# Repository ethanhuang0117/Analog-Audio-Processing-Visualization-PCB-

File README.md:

# Analog Audio Processing & Visualization PCB

A custom analog audio spectrum analyzer PCB that processes microphone audio across 8 frequency bands and displays signal intensity using 4-level LED indicators.

### Demo

[Download and Watch the PCB Demo](images/demo.mp4)

## Overview

The system captures audio through an electret microphone, amplifies the signal, separates it into 8 frequency bands using active filters, and displays the signal intensity through LED indicators.

**System Chain:**

Microphone → Preamp → 8-Band Filters → Envelope Detection → Comparators → LED Visualization

## Features

- 8 frequency bands spanning approximately 80 Hz – 10 kHz
- Cascaded Sallen-Key active filters for improved frequency separation
- Microphone preamplification for low-level audio signals
- Envelope detection to convert AC audio signals into DC levels
- 4-level LED intensity indication for each frequency band using comparators
- USB 5 V single-supply
- Custom PCB designed and assembled in KiCad

## Frequency Bands

| Band | Centre Frequency |
|---|---:|
| 1 | 80 Hz |
| 2 | 160 Hz |
| 3 | 320 Hz |
| 4 | 640 Hz |
| 5 | 1.25 kHz |
| 6 | 2.5 kHz |
| 7 | 5 kHz |
| 8 | 10 kHz |

## Filter Design

The initial design used passive filters, but were redesigned using cascaded Sallen-Key active filters to achieve greater roll-off and band separation.

### Sallen-Key Bandpass Filter Calculations

Each frequency band consists of a cascaded 2nd order Sallen-Key High Pass Filter (HPF) and Low Pass Filter (LPF).

**Assumptions:**
- $R_1 = R_2 = R$
- $C_1 = C_2 = C$
- $C = 100\text{nF}$ (Bands 1-4), $C = 10\text{nF}$ (Bands 5-8)

The cutoff frequencies are spaced by $\sqrt{2}$ from the centre frequency.

$$f_H = f_0 \times \sqrt{2}$$

$$f_L = \frac{f_0}{\sqrt{2}}$$

The general Sallen-Key cutoff frequency formula before simplification is:

$$f = \frac{1}{2\pi\sqrt{R_1 R_2 C_1 C_2}}$$

Applying the assumptions $R_1 = R_2 = R$ and $C_1 = C_2 = C$, this simplifies to:

$$f = \frac{1}{2\pi RC}$$

Rearranging for $R$:

$$R = \frac{1}{2\pi f C}$$

---

### Band 4 Example (Centre frequency: 640Hz)

**Step 1: Calculate HPF cutoff frequency**

$$f_L = \frac{f_0}{\sqrt{2}} = \frac{640}{\sqrt{2}} = 453\text{Hz}$$

**Step 2: Calculate LPF cutoff frequency**

$$f_H = f_0 \times \sqrt{2} = 640 \times \sqrt{2} = 905\text{Hz}$$

**Step 3: Calculate HPF resistor value ($C = 100\text{nF}$)**

$$R_{HPF} = \frac{1}{2\pi \times 453 \times 100 \times 10^{-9}} = 3513\Omega \approx 3.6\text{k}\Omega$$

**Step 4: Calculate LPF resistor value ($C = 100\text{nF}$)**

$$R_{LPF} = \frac{1}{2\pi \times 905 \times 100 \times 10^{-9}} = 1759\Omega \approx 1.8\text{k}\Omega$$

---

### Filter Band Summary

| Band | Centre Frequency | C | HPF Cutoff | HPF R | LPF Cutoff | LPF R |
|------|-----------------|---|------------|-------|------------|-------|
| 1 | 80Hz | 100nF | 56.6Hz | 27kΩ | 113Hz | 15kΩ |
| 2 | 160Hz | 100nF | 113Hz | 15kΩ | 226Hz | 6.8kΩ |
| 3 | 320Hz | 100nF | 226Hz | 6.8kΩ | 453Hz | 3.6kΩ |
| 4 | 640Hz | 100nF | 453Hz | 3.6kΩ | 905Hz | 1.8kΩ |
| 5 | 1.25kHz | 10nF | 884Hz | 18kΩ | 1.77kHz | 9.1kΩ |
| 6 | 2.5kHz | 10nF | 1.77kHz | 9.1kΩ | 3.54kHz | 4.7kΩ |
| 7 | 5kHz | 10nF | 3.54kHz | 4.7kΩ | 7.07kHz | 2.2kΩ |
| 8 | 10kHz | 10nF | 7.07kHz | 2.2kΩ | 14.1kHz | 1.1kΩ |

## Circuit Design

### Power

The circuit operates from a 5 V USB supply. Since audio signals oscillate about a center point, a virtual ground of 2.5V is used to allow the analog signal stages to operate from a single supply.

### Microphone & Preamplifier

A CMA-4544PF-W electret microphone captures the incoming audio signal, which is amplified using an MCP6004 op-amp to provide a suitable signal level for the filter stages.

The CMA-4544PF-W was chosen because its frequency response of 20Hz-20kHz covers the full audio spectrum.

### Envelope Detection

Each filtered signal passes through an envelope detector to convert the AC waveform into a varying DC voltage proportional to its amplitude.

The RC time constant determines the decay time of the envelope:

$$\tau = R \times C = 47\text{k}\Omega \times 4.7\mu\text{F} = 221\text{ms}$$

This gives a smooth, natural decay that visually tracks the music without flickering too fast or responding too sluggishly.

### Comparator & LED Stage

Comparator circuits divide each detected signal into four amplitude thresholds. The resulting outputs drive four LEDs per frequency band to provide a 4-level visualization of audio intensity.

## Prototyping & Testing

Individual circuit stages were first tested on breadboards and simulated in Multisim before PCB fabrication.

This iterative testing helped identify design issues before fabrication and reduced the need for PCB rework.

## PCB Design

The validated circuit was translated into a custom PCB using KiCad, with component placement, routing, and ground pours optimized for a compact and reliable layout.

### 3D PCB View

### Schematic

[View Full Schematic (PDF)](Schematic.pdf)

## Results

The completed PCB successfully processes audio through the 8 frequency bands and provides visual feedback through the LED array.

## Design Challenges & Iterations

### Passive → Active Filter Redesign

The original passive filter approach did not provide sufficient frequency separation. Sallen-Key active filters were implemented to improve roll-off and isolation between adjacent bands.

### Gain Optimization

The preamplifier gain was iteratively adjusted during breadboard testing to provide sufficient signal amplitude without excessive amplification of noise.

### Single-Supply Operation

Because the circuit operates from a 5 V USB supply, a virtual ground was implemented to allow the op-amp stages to process audio signals within the available supply range.

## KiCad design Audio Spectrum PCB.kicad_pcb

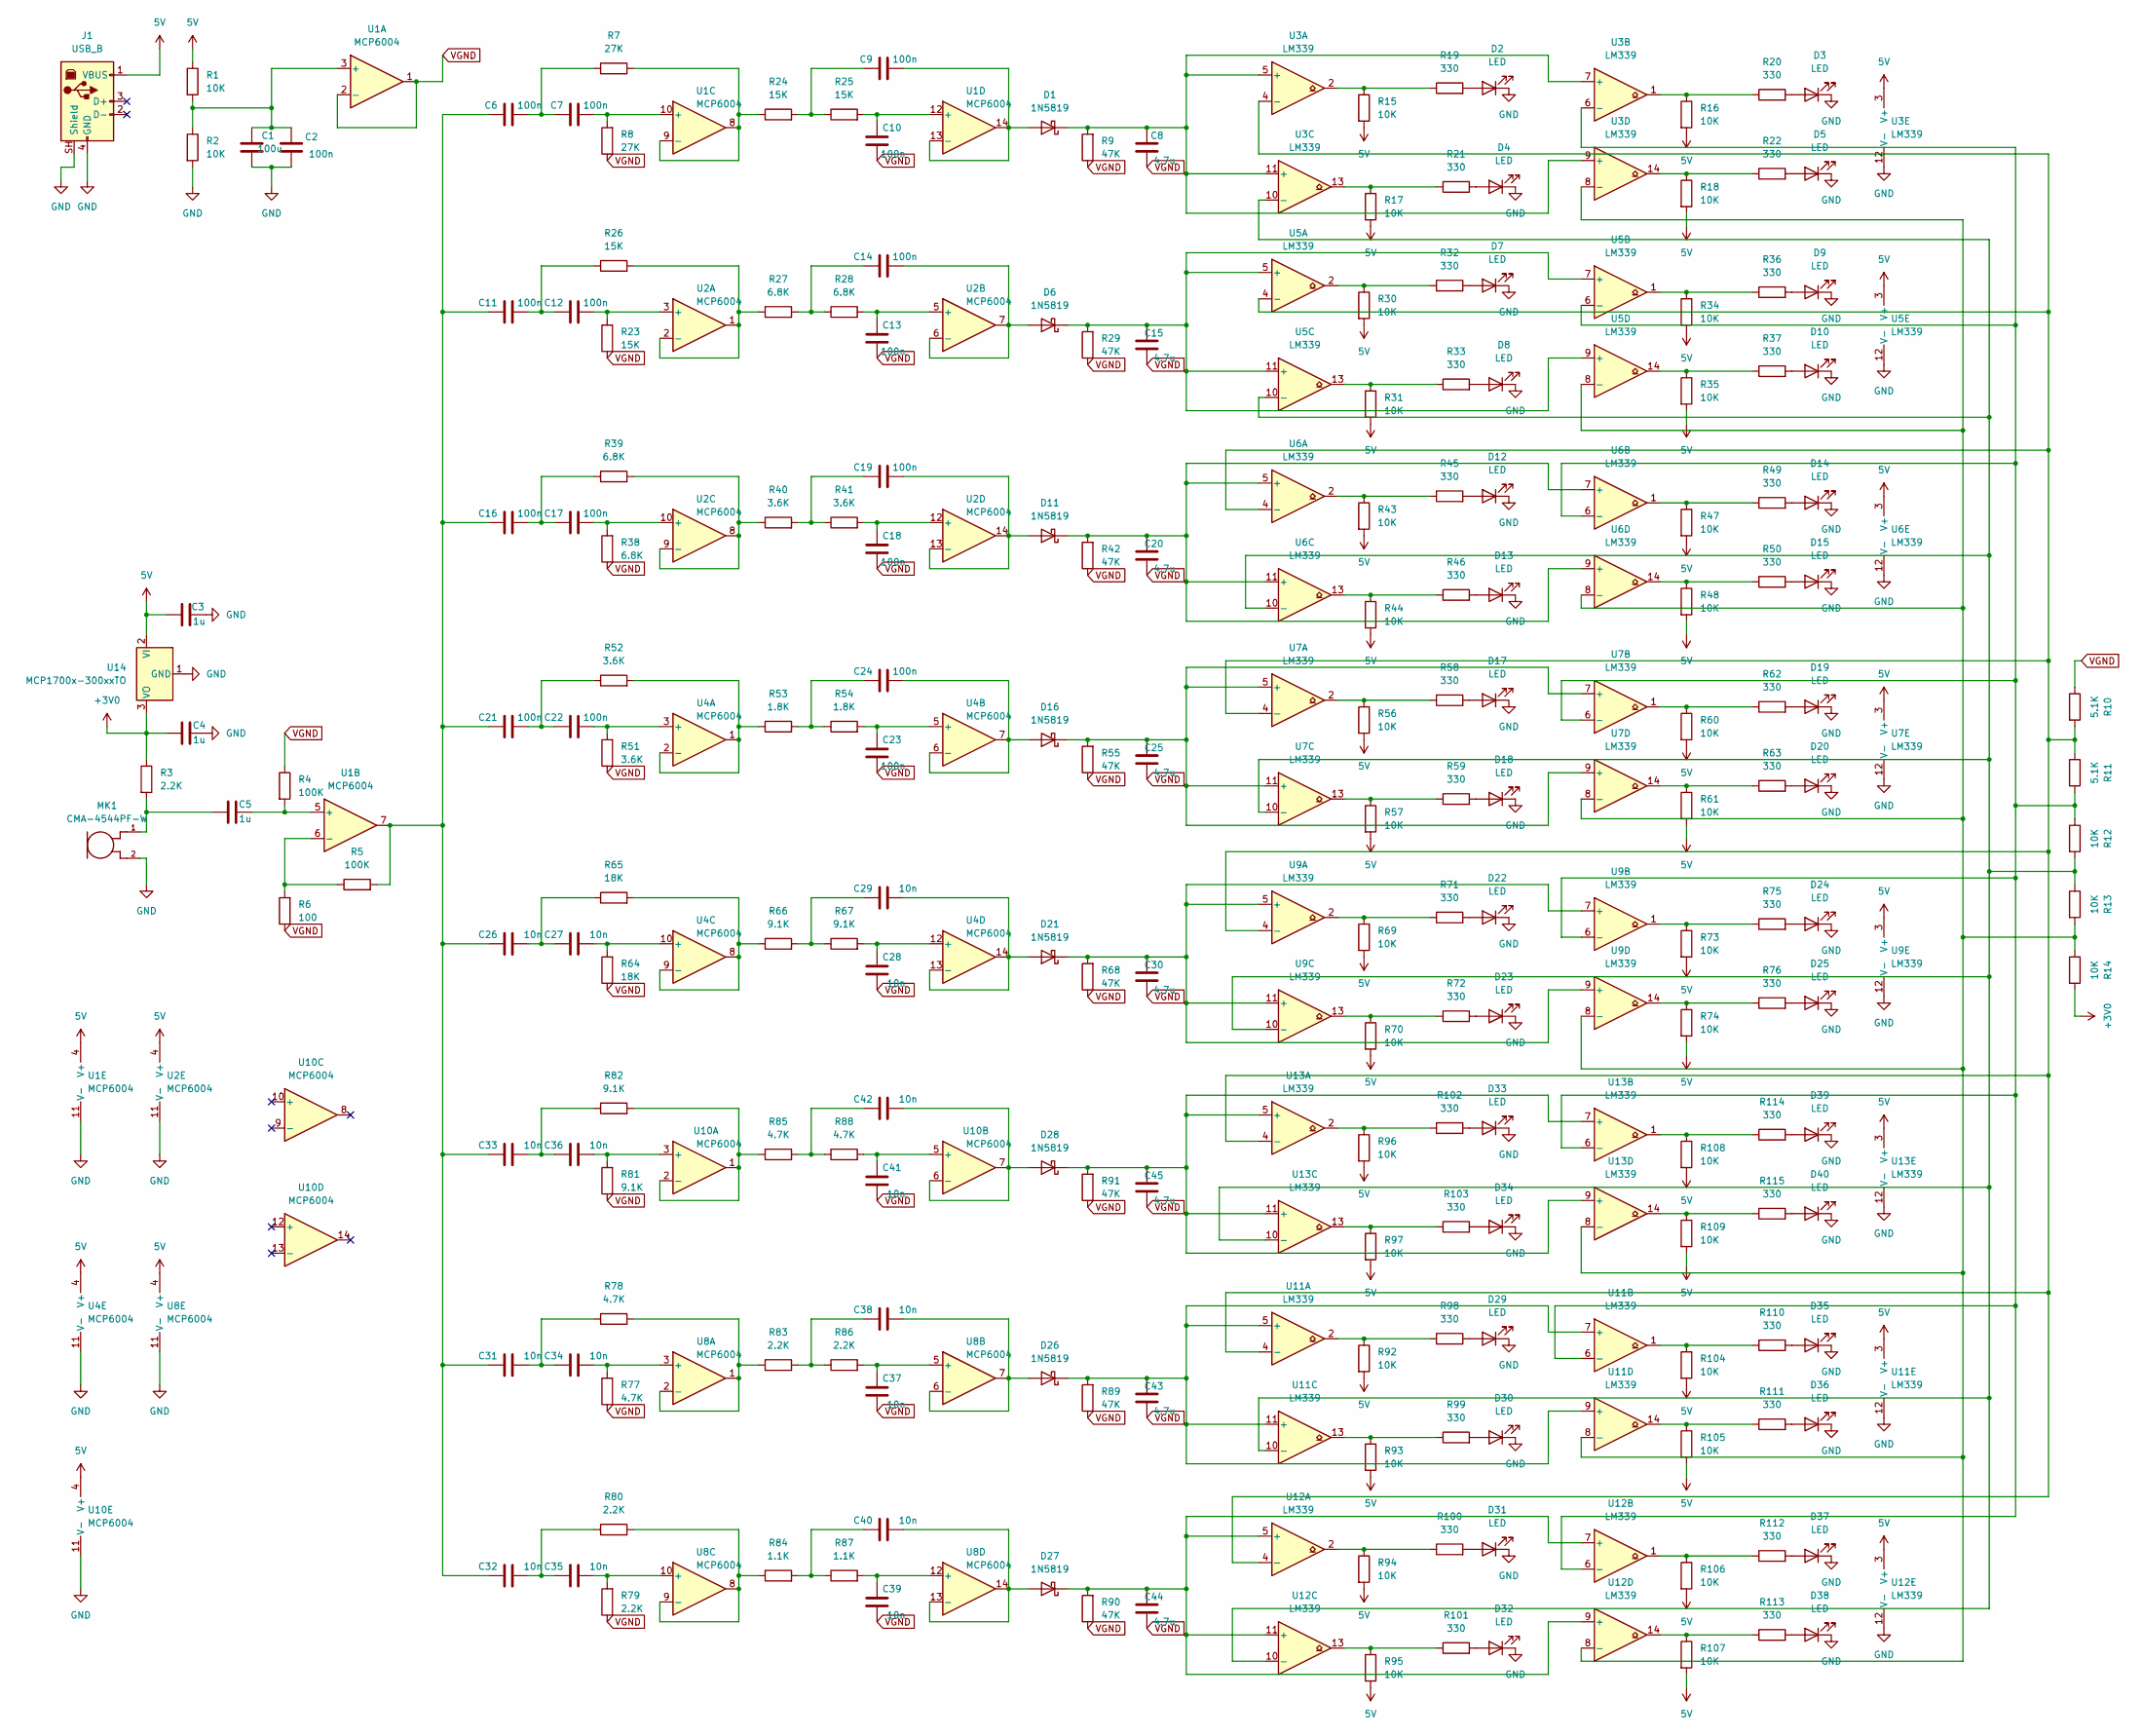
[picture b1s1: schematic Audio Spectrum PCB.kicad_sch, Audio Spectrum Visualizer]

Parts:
C1: 100u; CP_Radial_D5.0mm_P2.00mm
C2, C6, C7, C9, C10, C11, C12, C13, C14, C16, C17, C18, C19, C21, C22, C23, C24: 100n; C_Disc_D5.0mm_W2.5mm_P2.50mm
C3, C4, C5: 1u; CP_Radial_D5.0mm_P2.00mm
C8, C15, C20, C25, C30, C43, C44, C45: 4.7u; CP_Radial_D5.0mm_P2.00mm
C26, C27, C28, C29, C31, C32, C33, C34, C35, C36, C37, C38, C39, C40, C41, C42: 10n; C_Disc_D5.0mm_W2.5mm_P5.00mm
D1, D6, D11, D16, D21, D26, D27, D28: 1N5819; D_DO-41_SOD81_P10.16mm_Horizontal
D2, D3, D4, D5, D7, D8, D9, D10, D12, D13, D14, D15, D17, D18, D19, D20, D22, D23, D24, D25, D29, D30, D31, D32, D33, D34, D35, D36, D37, D38, D39, D40: LED; LED_D5.0mm
J1: USB_B; USB_B_OST_USB-B1HSxx_Horizontal
MK1: CMA-4544PF-W; MIC_CMA-4544PF-W
R1, R2, R12, R13, R14, R15, R16, R17, R18, R30, R31, R34, R35, R43, R44, R47, R48, R56, R57, R60, R61, R69, R70, R73, R74, R92, R93, R94, R95, R96, R97, R104, R105, R106, R107, R108, R109: 10K; R_Axial_DIN0207_L6.3mm_D2.5mm_P10.16mm_Horizontal
R3, R79, R80, R83, R86: 2.2K; R_Axial_DIN0207_L6.3mm_D2.5mm_P10.16mm_Horizontal
R4, R5: 100K; R_Axial_DIN0207_L6.3mm_D2.5mm_P10.16mm_Horizontal
R6: 100; R_Axial_DIN0207_L6.3mm_D2.5mm_P10.16mm_Horizontal
R7, R8: 27K; R_Axial_DIN0207_L6.3mm_D2.5mm_P10.16mm_Horizontal
R9, R29, R42, R55, R68, R89, R90, R91: 47K; R_Axial_DIN0207_L6.3mm_D2.5mm_P10.16mm_Horizontal
R10, R11: 5.1K; R_Axial_DIN0207_L6.3mm_D2.5mm_P10.16mm_Horizontal
R19, R20, R21, R22, R32, R33, R36, R37, R45, R46, R49, R50, R58, R59, R62, R63, R71, R72, R75, R76, R98, R99, R100, R101, R102, R103, R110, R111, R112, R113, R114, R115: 330; R_Axial_DIN0207_L6.3mm_D2.5mm_P10.16mm_Horizontal
R23, R24, R25, R26: 15K; R_Axial_DIN0207_L6.3mm_D2.5mm_P10.16mm_Horizontal
R27, R28, R38, R39: 6.8K; R_Axial_DIN0207_L6.3mm_D2.5mm_P10.16mm_Horizontal
R40, R41, R51, R52: 3.6K; R_Axial_DIN0207_L6.3mm_D2.5mm_P10.16mm_Horizontal
R53, R54: 1.8K; R_Axial_DIN0207_L6.3mm_D2.5mm_P10.16mm_Horizontal
R64, R65: 18K; R_Axial_DIN0207_L6.3mm_D2.5mm_P10.16mm_Horizontal
R66, R67, R81, R82: 9.1K; R_Axial_DIN0207_L6.3mm_D2.5mm_P10.16mm_Horizontal
R77, R78, R85, R88: 4.7K; R_Axial_DIN0207_L6.3mm_D2.5mm_P10.16mm_Horizontal
R84, R87: 1.1K; R_Axial_DIN0207_L6.3mm_D2.5mm_P10.16mm_Horizontal
U1, U2, U4, U8, U10: MCP6004; DIP-14_W7.62mm
U3, U5, U6, U7, U9, U11, U12, U13: LM339; DIP-14_W7.62mm
U14: MCP1700x-300xxTO; TO-92_Inline

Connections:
5V: C3.1, J1.1 (VBUS), R1.1, R15.2, R16.2, R17.2, R18.2, R30.2, R31.2, R34.2, R35.2, R43.2, R44.2, R47.2, R48.2, R56.2, R57.2, R60.2, R61.2, R69.2, R70.2, R73.2, R74.2, R92.2, R93.2, R94.2, R95.2, R96.2, R97.2, R104.2, R105.2, R106.2, R107.2, R108.2, R109.2, U1.4 (V+), U2.4 (V+), U3.3 (V+), U4.4 (V+), U5.3 (V+), U6.3 (V+), U7.3 (V+), U8.4 (V+), U9.3 (V+), U10.4 (V+), U11.3 (V+), U12.3 (V+), U13.3 (V+), U14.2 (VI)
+3V0: C4.1, R3.1, R14.2, U14.3 (VO)
GND: C1.2, C2.2, C3.2, C4.2, D2.1 (K), D3.1 (K), D4.1 (K), D5.1 (K), D7.1 (K), D8.1 (K), D9.1 (K), D10.1 (K), D12.1 (K), D13.1 (K), D14.1 (K), D15.1 (K), D17.1 (K), D18.1 (K), D19.1 (K), D20.1 (K), D22.1 (K), D23.1 (K), D24.1 (K), D25.1 (K), D29.1 (K), D30.1 (K), D31.1 (K), D32.1 (K), D33.1 (K), D34.1 (K), D35.1 (K), D36.1 (K), D37.1 (K), D38.1 (K), D39.1 (K), D40.1 (K), J1.4 (GND), J1.SH (Shield), MK1.2, R2.2, U1.11 (V-), U2.11 (V-), U3.12 (V-), U4.11 (V-), U5.12 (V-), U6.12 (V-), U7.12 (V-), U8.11 (V-), U9.12 (V-), U10.11 (V-), U11.12 (V-), U12.12 (V-), U13.12 (V-), U14.1 (GND)
unnamed: C5.1, MK1.1, R3.2
unnamed: C6.2, C7.1, R7.1
unnamed: C9.1, R24.2, R25.1
unnamed: C6.1, C11.1, C16.1, C21.1, C26.1, C31.1, C32.1, C33.1, R5.2, U1.7
unnamed: C11.2, C12.1, R26.1
unnamed: C14.1, R27.2, R28.1
unnamed: C16.2, C17.1, R39.1
unnamed: C19.1, R40.2, R41.1
unnamed: C21.2, C22.1, R52.1
unnamed: C24.1, R53.2, R54.1
unnamed: C26.2, C27.1, R65.1
unnamed: C29.1, R66.2, R67.1
unnamed: C31.2, C34.1, R78.1
unnamed: C32.2, C35.1, R80.1
unnamed: C33.2, C36.1, R82.1
unnamed: C38.1, R83.2, R86.1
unnamed: C40.1, R84.2, R87.1
unnamed: C42.1, R85.2, R88.1
unnamed: C9.2, D1.2 (A), U1.13 (-), U1.14
unnamed: C8.2, D1.1 (K), R9.2, U3.5 (+), U3.7 (+), U3.9 (+), U3.11 (+)
unnamed: D2.2 (A), R19.2
unnamed: D3.2 (A), R20.2
unnamed: D4.2 (A), R21.2
unnamed: D5.2 (A), R22.2
unnamed: C14.2, D6.2 (A), U2.6 (-), U2.7
unnamed: C15.2, D6.1 (K), R29.2, U5.5 (+), U5.7 (+), U5.9 (+), U5.11 (+)
unnamed: D7.2 (A), R32.2
unnamed: D8.2 (A), R33.2
unnamed: D9.2 (A), R36.2
unnamed: D10.2 (A), R37.2
unnamed: C19.2, D11.2 (A), U2.13 (-), U2.14
unnamed: C20.2, D11.1 (K), R42.2, U6.5 (+), U6.7 (+), U6.9 (+), U6.11 (+)
unnamed: D12.2 (A), R45.2
unnamed: D13.2 (A), R46.2
unnamed: D14.2 (A), R49.2
unnamed: D15.2 (A), R50.2
unnamed: C24.2, D16.2 (A), U4.6 (-), U4.7
unnamed: C25.2, D16.1 (K), R55.2, U7.5 (+), U7.7 (+), U7.9 (+), U7.11 (+)
unnamed: D17.2 (A), R58.2
unnamed: D18.2 (A), R59.2
unnamed: D19.2 (A), R62.2
unnamed: D20.2 (A), R63.2
unnamed: C29.2, D21.2 (A), U4.13 (-), U4.14
unnamed: C30.2, D21.1 (K), R68.2, U9.5 (+), U9.7 (+), U9.9 (+), U9.11 (+)
unnamed: D22.2 (A), R71.2
unnamed: D23.2 (A), R72.2
unnamed: D24.2 (A), R75.2
unnamed: D25.2 (A), R76.2
unnamed: C38.2, D26.2 (A), U8.6 (-), U8.7
unnamed: C43.2, D26.1 (K), R89.2, U11.5 (+), U11.7 (+), U11.9 (+), U11.11 (+)
unnamed: C40.2, D27.2 (A), U8.13 (-), U8.14
unnamed: C44.2, D27.1 (K), R90.2, U12.5 (+), U12.7 (+), U12.9 (+), U12.11 (+)
unnamed: C42.2, D28.2 (A), U10.6 (-), U10.7
unnamed: C45.2, D28.1 (K), R91.2, U13.5 (+), U13.7 (+), U13.9 (+), U13.11 (+)
unnamed: D29.2 (A), R98.2
unnamed: D30.2 (A), R99.2
unnamed: D31.2 (A), R100.2
unnamed: D32.2 (A), R101.2
unnamed: D33.2 (A), R102.2
unnamed: D34.2 (A), R103.2
unnamed: D35.2 (A), R110.2
unnamed: D36.2 (A), R111.2
unnamed: D37.2 (A), R112.2
unnamed: D38.2 (A), R113.2
unnamed: D39.2 (A), R114.2
unnamed: D40.2 (A), R115.2
unnamed: R15.1, R19.1, U3.2
unnamed: R16.1, R20.1, U3.1
unnamed: R17.1, R21.1, U3.13
unnamed: R18.1, R22.1, U3.14
unnamed: R30.1, R32.1, U5.2
unnamed: R31.1, R33.1, U5.13
unnamed: R34.1, R36.1, U5.1
unnamed: R35.1, R37.1, U5.14
unnamed: R43.1, R45.1, U6.2
unnamed: R44.1, R46.1, U6.13
unnamed: R47.1, R49.1, U6.1
unnamed: R48.1, R50.1, U6.14
unnamed: R56.1, R58.1, U7.2
unnamed: R57.1, R59.1, U7.13
unnamed: R60.1, R62.1, U7.1
unnamed: R61.1, R63.1, U7.14
unnamed: R69.1, R71.1, U9.2
unnamed: R70.1, R72.1, U9.13
unnamed: R73.1, R75.1, U9.1
unnamed: R74.1, R76.1, U9.14
unnamed: R92.1, R98.1, U11.2
unnamed: R93.1, R99.1, U11.13
unnamed: R94.1, R100.1, U12.2
unnamed: R95.1, R101.1, U12.13
unnamed: R96.1, R102.1, U13.2
unnamed: R97.1, R103.1, U13.13
unnamed: R104.1, R110.1, U11.1
unnamed: R105.1, R111.1, U11.14
unnamed: R106.1, R112.1, U12.1
unnamed: R107.1, R113.1, U12.14
unnamed: R108.1, R114.1, U13.1
unnamed: R109.1, R115.1, U13.14
unnamed: C1.1, C2.1, R1.2, R2.1, U1.3 (+)
unnamed: C5.2, R4.2, U1.5 (+)
unnamed: R5.1, R6.2, U1.6 (-)
unnamed: C7.2, R8.2, U1.10 (+)
unnamed: R7.2, R24.1, U1.8, U1.9 (-)
unnamed: C10.2, R25.2, U1.12 (+)
unnamed: C12.2, R23.2, U2.3 (+)
unnamed: R26.2, R27.1, U2.1, U2.2 (-)
unnamed: C13.2, R28.2, U2.5 (+)
unnamed: C17.2, R38.2, U2.10 (+)
unnamed: R39.2, R40.1, U2.8, U2.9 (-)
unnamed: C18.2, R41.2, U2.12 (+)
unnamed: C22.2, R51.2, U4.3 (+)
unnamed: R52.2, R53.1, U4.1, U4.2 (-)
unnamed: C23.2, R54.2, U4.5 (+)
unnamed: C27.2, R64.2, U4.10 (+)
unnamed: R65.2, R66.1, U4.8, U4.9 (-)
unnamed: C28.2, R67.2, U4.12 (+)
unnamed: C34.2, R77.2, U8.3 (+)
unnamed: R78.2, R83.1, U8.1, U8.2 (-)
unnamed: C37.2, R86.2, U8.5 (+)
unnamed: C35.2, R79.2, U8.10 (+)
unnamed: R80.2, R84.1, U8.8, U8.9 (-)
unnamed: C39.2, R87.2, U8.12 (+)
unnamed: C36.2, R81.2, U10.3 (+)
unnamed: R82.2, R85.1, U10.1, U10.2 (-)
unnamed: C41.2, R88.2, U10.5 (+)
unnamed: R10.2, R11.1, U3.4 (-), U5.4 (-), U6.4 (-), U7.4 (-), U9.4 (-), U11.4 (-), U12.4 (-), U13.4 (-)
unnamed: R11.2, R12.1, U3.6 (-), U5.6 (-), U6.6 (-), U7.6 (-), U9.6 (-), U11.6 (-), U12.6 (-), U13.6 (-)
unnamed: R12.2, R13.1, U3.10 (-), U5.10 (-), U6.10 (-), U7.10 (-), U9.10 (-), U11.10 (-), U12.10 (-), U13.10 (-)
unnamed: R13.2, R14.1, U3.8 (-), U5.8 (-), U6.8 (-), U7.8 (-), U9.8 (-), U11.8 (-), U12.8 (-), U13.8 (-)
VGND: C8.1, C10.1, C13.1, C15.1, C18.1, C20.1, C23.1, C25.1, C28.1, C30.1, C37.1, C39.1, C41.1, C43.1, C44.1, C45.1, R4.1, R6.1, R8.1, R9.1, R10.1, R23.1, R29.1, R38.1, R42.1, R51.1, R55.1, R64.1, R68.1, R77.1, R79.1, R81.1, R89.1, R90.1, R91.1, U1.1, U1.2 (-)

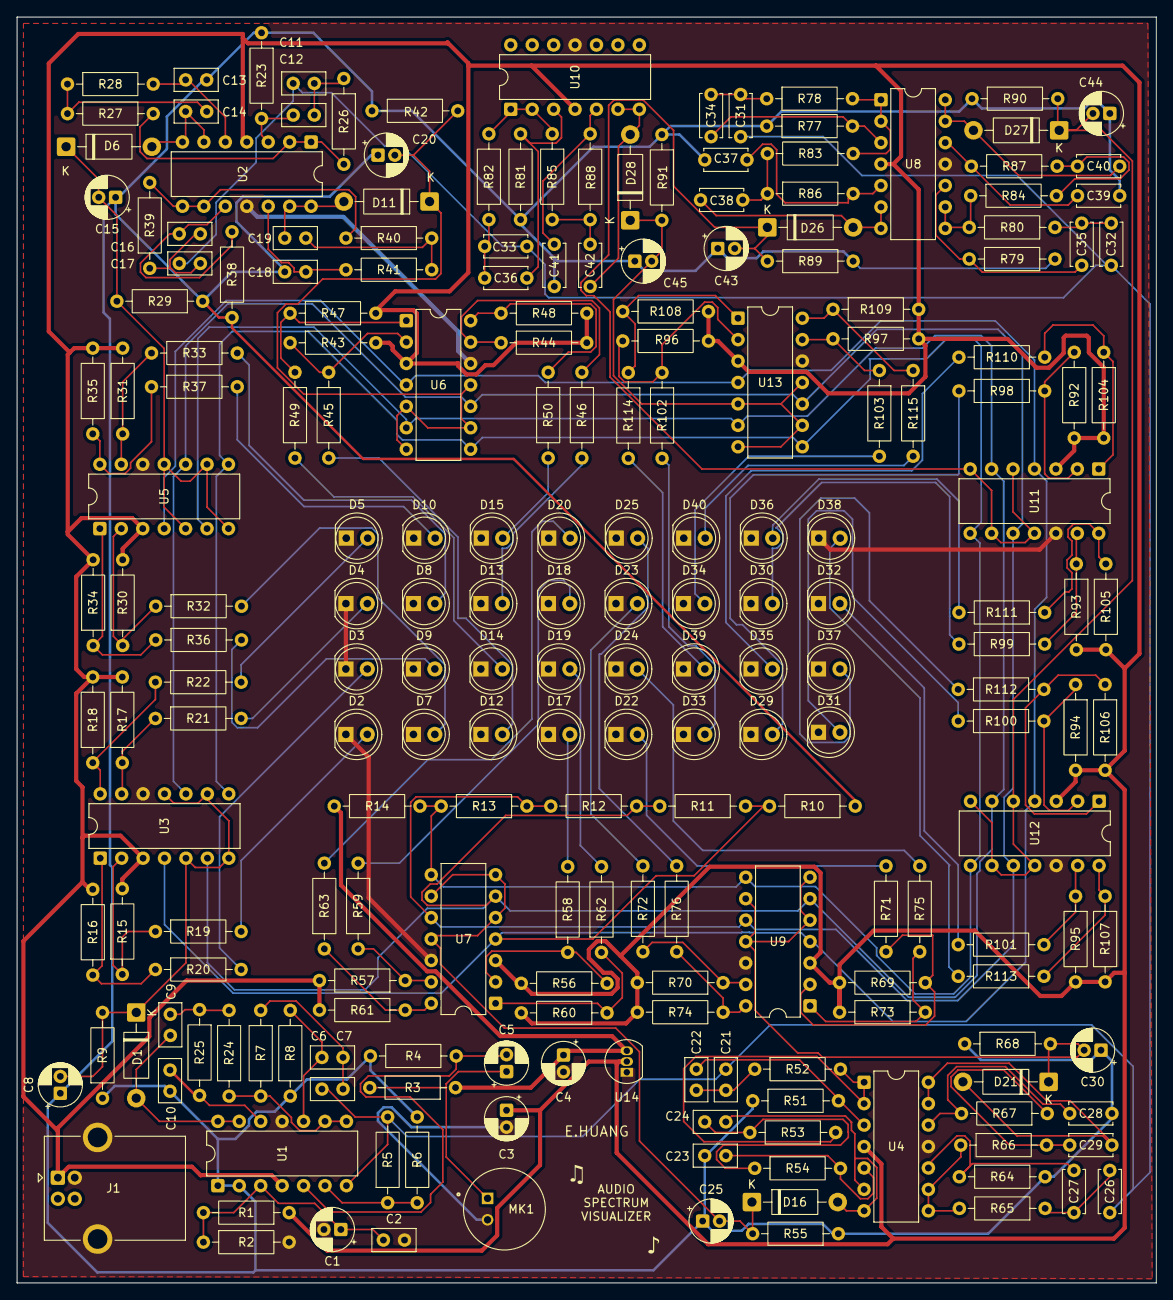
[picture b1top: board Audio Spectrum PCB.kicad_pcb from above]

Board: 2 copper layers, 135.0 x 150.0 mm, 216 parts (0 on the bottom side), 133 nets.
